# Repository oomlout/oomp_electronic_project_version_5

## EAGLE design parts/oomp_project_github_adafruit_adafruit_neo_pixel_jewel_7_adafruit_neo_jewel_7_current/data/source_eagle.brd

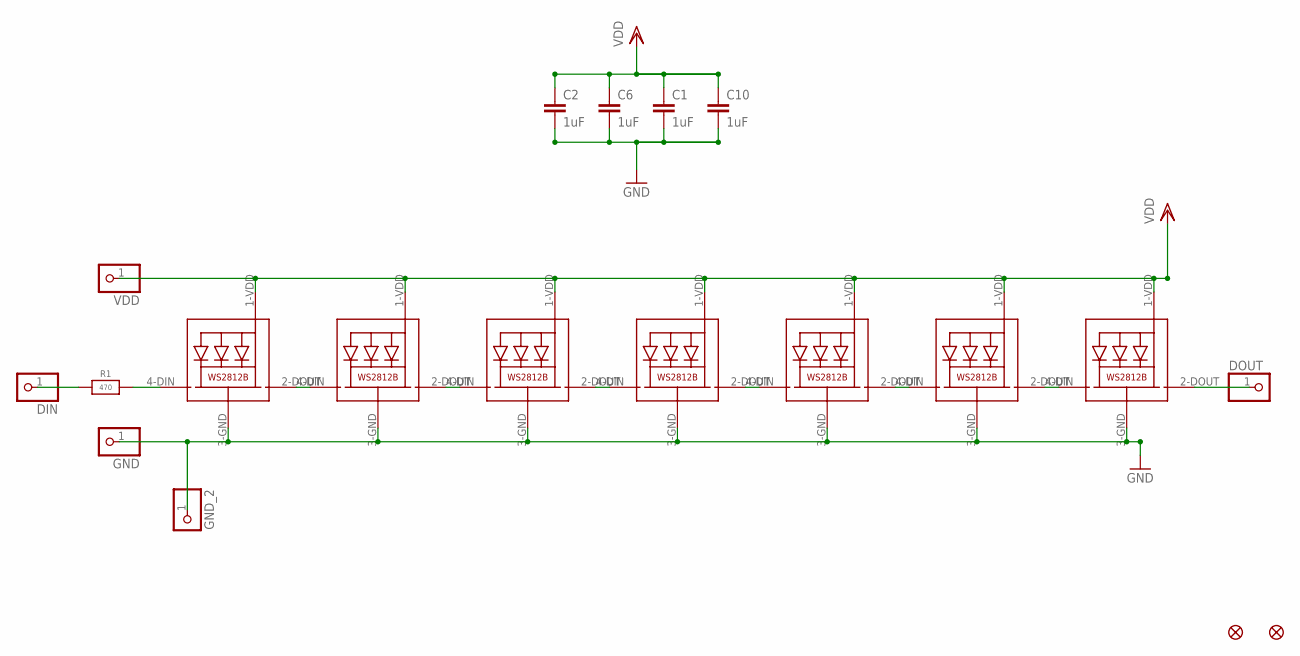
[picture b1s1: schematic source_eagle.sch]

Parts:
C1, C2, C6, C10: 1uF; C0603
DIN: PINHD-1X1CB; 1X01-CLEANBIG
DOUT: PINHD-1X1CB; 1X01-CLEANBIG
FID1, FID2: FIDUCIAL""; FIDUCIAL_1MM
GND: PINHD-1X1CB; 1X01-CLEANBIG
GND_2: PINHD-1X1CB; 1X01-CLEANBIG
LED1, LED2, LED3, LED4, LED5, LED6, LED7: WS2812B5050; WS2812B
R1: 470; 0603-NO
VDD: PINHD-1X1CB; 1X01-CLEANBIG

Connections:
GND: C1.2, C2.2, C6.2, C10.2, GND.1, GND_2.1, LED1.3-GND (GND), LED2.3-GND (GND), LED3.3-GND (GND), LED4.3-GND (GND), LED5.3-GND (GND), LED6.3-GND (GND), LED7.3-GND (GND)
unnamed: LED1.2-DOUT (DO), LED2.4-DIN (DI)
unnamed: LED2.2-DOUT (DO), LED3.4-DIN (DI)
unnamed: LED3.2-DOUT (DO), LED4.4-DIN (DI)
unnamed: LED4.2-DOUT (DO), LED5.4-DIN (DI)
unnamed: LED5.2-DOUT (DO), LED6.4-DIN (DI)
unnamed: LED6.2-DOUT (DO), LED7.4-DIN (DI)
unnamed: DOUT.1, LED7.2-DOUT (DO)
unnamed: LED1.4-DIN (DI), R1.2
unnamed: DIN.1, R1.1
VDD: C1.1, C2.1, C6.1, C10.1, LED1.1-VDD (VDD), LED2.1-VDD (VDD), LED3.1-VDD (VDD), LED4.1-VDD (VDD), LED5.1-VDD (VDD), LED6.1-VDD (VDD), LED7.1-VDD (VDD), VDD.1

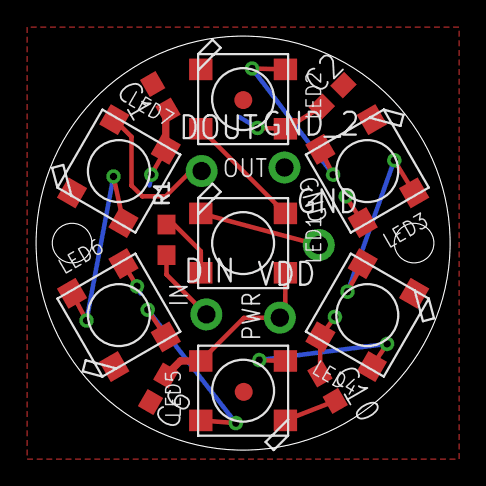
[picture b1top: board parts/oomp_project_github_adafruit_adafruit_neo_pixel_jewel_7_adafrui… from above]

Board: 2 copper layers, 23.0 x 23.0 mm, 20 parts (1 on the bottom side), 11 nets.

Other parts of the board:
U$3: ADAFRUIT_5MM

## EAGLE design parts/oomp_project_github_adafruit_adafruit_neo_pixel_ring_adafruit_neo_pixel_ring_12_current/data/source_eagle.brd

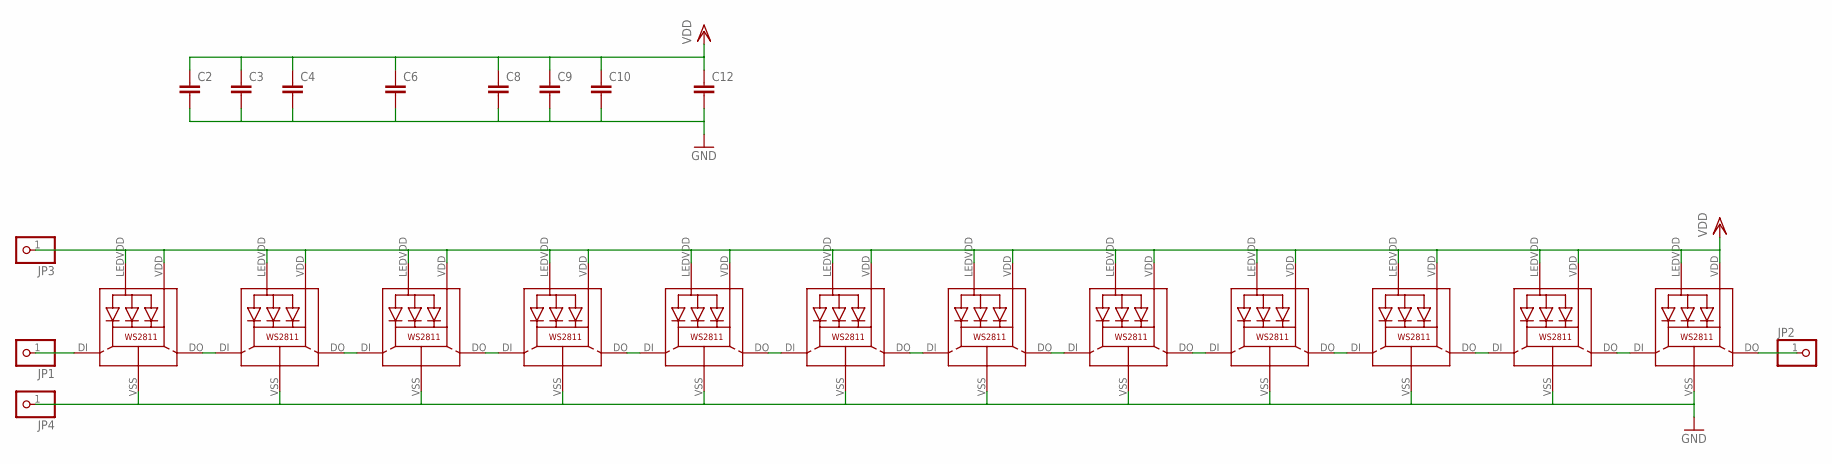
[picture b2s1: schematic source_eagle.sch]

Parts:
C2, C3, C4, C6, C8, C9, C10, C12: C-EUC0603; C0603
JP1, JP2, JP3, JP4: PINHD-1X1CB; 1X01-CLEANBIG
LED1, LED2, LED3, LED4, LED5, LED6, LED7, LED8, LED9, LED10, LED11, LED12: WS28115050

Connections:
GND: C2.2, C3.2, C4.2, C6.2, C8.2, C9.2, C10.2, C12.2, JP4.1, LED1.VSS (GND), LED2.VSS (GND), LED3.VSS (GND), LED4.VSS (GND), LED5.VSS (GND), LED6.VSS (GND), LED7.VSS (GND), LED8.VSS (GND), LED9.VSS (GND), LED10.VSS (GND), LED11.VSS (GND), LED12.VSS (GND)
unnamed: LED1.DO, LED2.DI
unnamed: LED2.DO, LED3.DI
unnamed: LED3.DO, LED4.DI
unnamed: LED4.DO, LED5.DI
unnamed: LED5.DO, LED6.DI
unnamed: LED6.DO, LED7.DI
unnamed: LED7.DO, LED8.DI
unnamed: LED8.DO, LED9.DI
unnamed: LED9.DO, LED10.DI
unnamed: LED10.DO, LED11.DI
unnamed: LED11.DO, LED12.DI
unnamed: JP1.1, LED1.DI
unnamed: JP2.1, LED12.DO
VDD: C2.1, C3.1, C4.1, C6.1, C8.1, C9.1, C10.1, C12.1, JP3.1, LED1.LEDVDD, LED1.VDD, LED2.LEDVDD, LED2.VDD, LED3.LEDVDD, LED3.VDD, LED4.LEDVDD, LED4.VDD, LED5.LEDVDD, LED5.VDD, LED6.LEDVDD, LED6.VDD, LED7.LEDVDD, LED7.VDD, LED8.LEDVDD, LED8.VDD, LED9.LEDVDD, LED9.VDD, LED10.LEDVDD, LED10.VDD, LED11.LEDVDD, LED11.VDD, LED12.LEDVDD, LED12.VDD

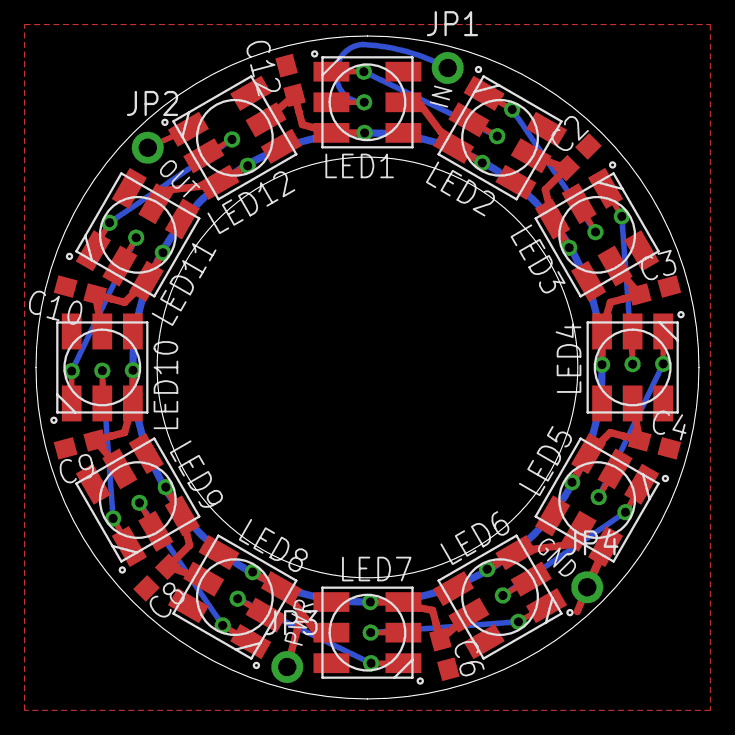
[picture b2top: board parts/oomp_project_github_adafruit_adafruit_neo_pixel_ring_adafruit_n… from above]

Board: 2 copper layers, 36.8 x 36.8 mm, 27 parts (1 on the bottom side), 15 nets.

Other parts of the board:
U$1, U$2: GUIDE-STAR-12
U$3: ADAFRUIT_5MM

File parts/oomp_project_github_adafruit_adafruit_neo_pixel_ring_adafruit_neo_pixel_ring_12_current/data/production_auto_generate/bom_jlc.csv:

Comment,Designator,Footprint,LCSC Part #
,"JP1,JP2,JP3,JP4",Adafruit NeoPixel Ring 12-import-fps:1X01-CLEANBIG,C7501259
,U$3,Adafruit NeoPixel Ring 12-import-fps:ADAFRUIT_5MM,
,"C2,C3,C4,C6,C8,C9,C10,C12",Adafruit NeoPixel Ring 12-import-fps:C0603,
,"U$1,U$2",Adafruit NeoPixel Ring 12-import-fps:GUIDE-STAR-12,
WS28115050,"LED1,LED2,LED3,LED4,LED5,LED6,LED7,LED8,LED9,LED10,LED11,LED12",Adafruit NeoPixel Ring 12-import-fps:WS28115050,

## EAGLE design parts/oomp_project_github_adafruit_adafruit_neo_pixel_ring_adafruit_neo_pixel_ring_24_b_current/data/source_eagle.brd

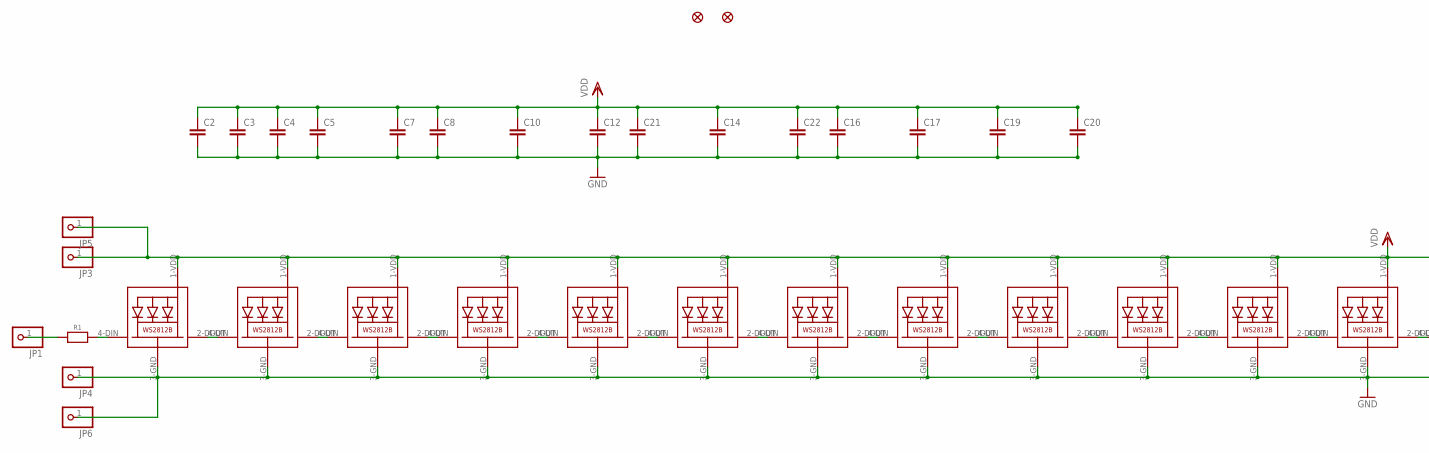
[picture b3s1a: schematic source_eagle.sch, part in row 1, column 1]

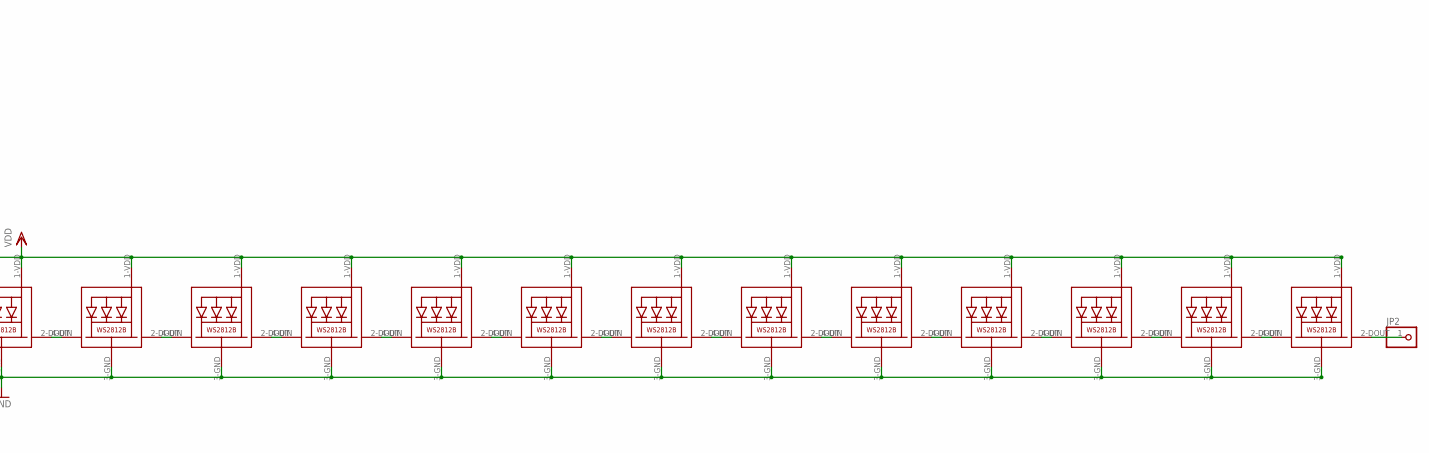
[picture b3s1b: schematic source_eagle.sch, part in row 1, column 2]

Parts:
C2, C3, C4, C5, C7, C8, C10, C12, C14, C16, C17, C19, C20, C21, C22: C-EUC0603; C0603
FID1, FID2: FIDUCIAL""; FIDUCIAL_1MM
JP1, JP2, JP3, JP4, JP5, JP6: PINHD-1X1CB; 1X01-CLEANBIG
LED1, LED2, LED3, LED4, LED5, LED6, LED7, LED8, LED9, LED10, LED11, LED12, LED13, LED14, LED15, LED16, LED17, LED18, LED19, LED20, LED21, LED22, LED23, LED24: WS2812B5050; WS2812B
R1: RESISTOR_0603_NOOUT; 0603-NO

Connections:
GND: C2.2, C3.2, C4.2, C5.2, C7.2, C8.2, C10.2, C12.2, C14.2, C16.2, C17.2, C19.2, C20.2, C21.2, C22.2, JP4.1, JP6.1, LED1.3-GND (GND), LED2.3-GND (GND), LED3.3-GND (GND), LED4.3-GND (GND), LED5.3-GND (GND), LED6.3-GND (GND), LED7.3-GND (GND), LED8.3-GND (GND), LED9.3-GND (GND), LED10.3-GND (GND), LED11.3-GND (GND), LED12.3-GND (GND), LED13.3-GND (GND), LED14.3-GND (GND), LED15.3-GND (GND), LED16.3-GND (GND), LED17.3-GND (GND), LED18.3-GND (GND), LED19.3-GND (GND), LED20.3-GND (GND), LED21.3-GND (GND), LED22.3-GND (GND), LED23.3-GND (GND), LED24.3-GND (GND)
unnamed: LED1.2-DOUT (DO), LED2.4-DIN (DI)
unnamed: LED2.2-DOUT (DO), LED3.4-DIN (DI)
unnamed: LED3.2-DOUT (DO), LED4.4-DIN (DI)
unnamed: LED4.2-DOUT (DO), LED5.4-DIN (DI)
unnamed: LED5.2-DOUT (DO), LED6.4-DIN (DI)
unnamed: LED6.2-DOUT (DO), LED7.4-DIN (DI)
unnamed: LED7.2-DOUT (DO), LED8.4-DIN (DI)
unnamed: LED8.2-DOUT (DO), LED9.4-DIN (DI)
unnamed: LED9.2-DOUT (DO), LED10.4-DIN (DI)
unnamed: LED10.2-DOUT (DO), LED11.4-DIN (DI)
unnamed: LED11.2-DOUT (DO), LED12.4-DIN (DI)
unnamed: LED12.2-DOUT (DO), LED13.4-DIN (DI)
unnamed: LED13.2-DOUT (DO), LED14.4-DIN (DI)
unnamed: LED14.2-DOUT (DO), LED15.4-DIN (DI)
unnamed: LED15.2-DOUT (DO), LED16.4-DIN (DI)
unnamed: LED16.2-DOUT (DO), LED17.4-DIN (DI)
unnamed: LED17.2-DOUT (DO), LED18.4-DIN (DI)
unnamed: LED18.2-DOUT (DO), LED19.4-DIN (DI)
unnamed: LED19.2-DOUT (DO), LED20.4-DIN (DI)
unnamed: LED20.2-DOUT (DO), LED21.4-DIN (DI)
unnamed: LED21.2-DOUT (DO), LED22.4-DIN (DI)
unnamed: LED22.2-DOUT (DO), LED23.4-DIN (DI)
unnamed: LED23.2-DOUT (DO), LED24.4-DIN (DI)
unnamed: JP2.1, LED24.2-DOUT (DO)
unnamed: LED1.4-DIN (DI), R1.2
unnamed: JP1.1, R1.1
VDD: C2.1, C3.1, C4.1, C5.1, C7.1, C8.1, C10.1, C12.1, C14.1, C16.1, C17.1, C19.1, C20.1, C21.1, C22.1, JP3.1, JP5.1, LED1.1-VDD (VDD), LED2.1-VDD (VDD), LED3.1-VDD (VDD), LED4.1-VDD (VDD), LED5.1-VDD (VDD), LED6.1-VDD (VDD), LED7.1-VDD (VDD), LED8.1-VDD (VDD), LED9.1-VDD (VDD), LED10.1-VDD (VDD), LED11.1-VDD (VDD), LED12.1-VDD (VDD), LED13.1-VDD (VDD), LED14.1-VDD (VDD), LED15.1-VDD (VDD), LED16.1-VDD (VDD), LED17.1-VDD (VDD), LED18.1-VDD (VDD), LED19.1-VDD (VDD), LED20.1-VDD (VDD), LED21.1-VDD (VDD), LED22.1-VDD (VDD), LED23.1-VDD (VDD), LED24.1-VDD (VDD)

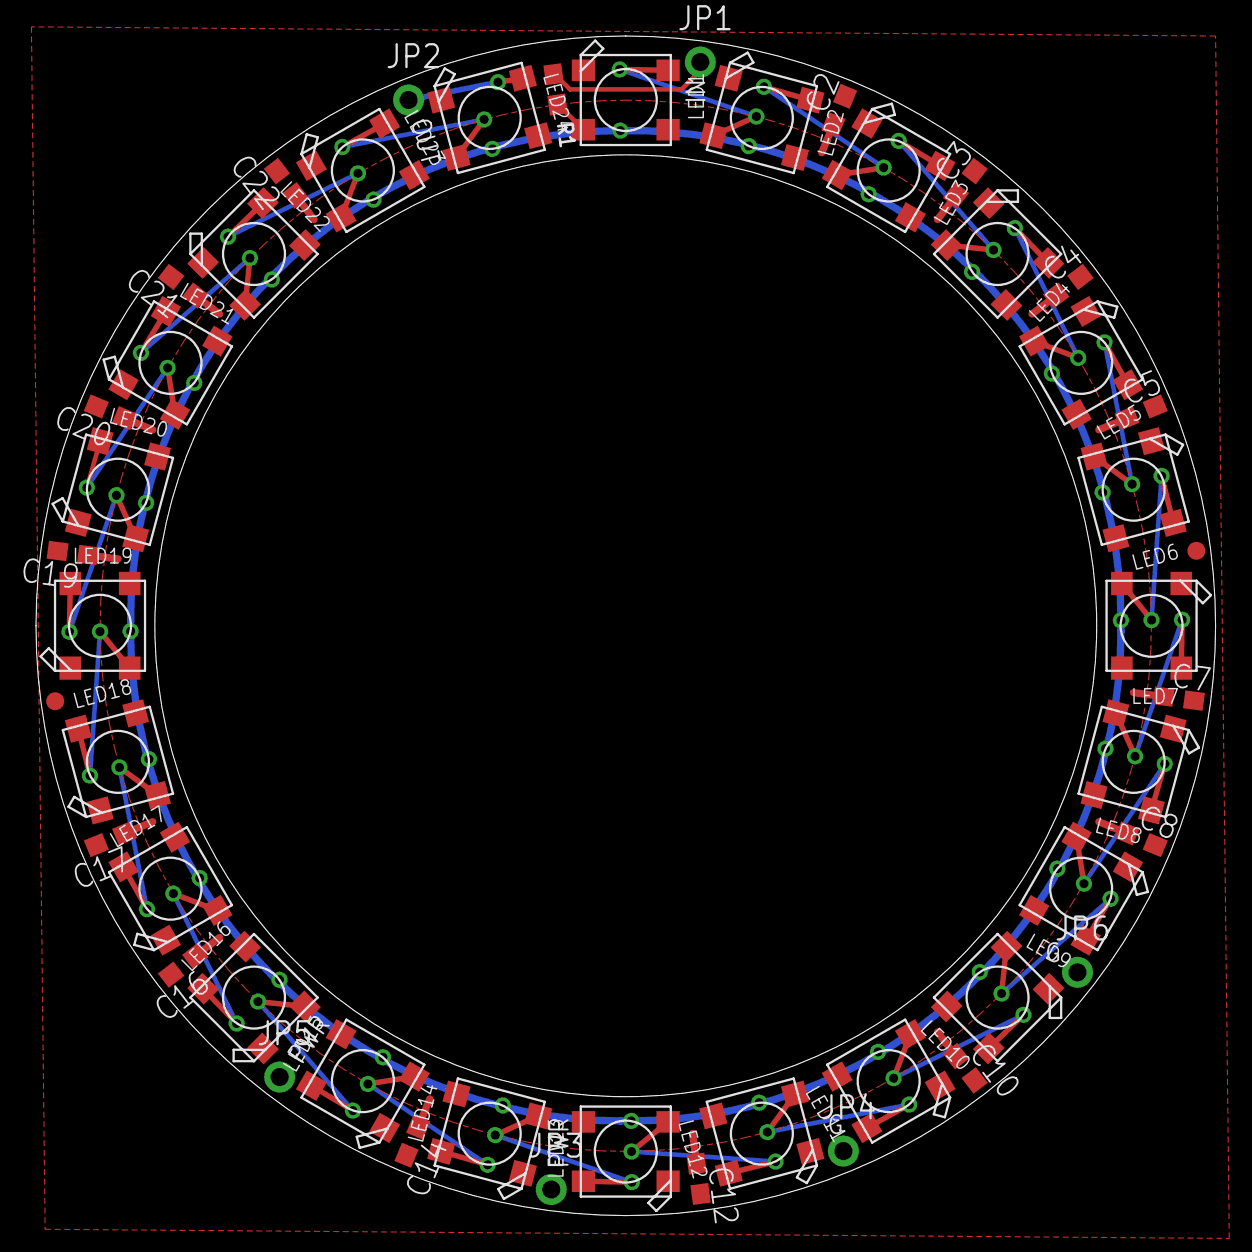
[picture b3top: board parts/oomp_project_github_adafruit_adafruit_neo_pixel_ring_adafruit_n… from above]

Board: 2 copper layers, 65.5 x 65.5 mm, 49 parts (1 on the bottom side), 28 nets.

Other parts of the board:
U$1: ADAFRUIT_5MM

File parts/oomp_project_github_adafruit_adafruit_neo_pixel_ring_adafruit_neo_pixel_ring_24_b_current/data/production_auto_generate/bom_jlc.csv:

Comment,Designator,Footprint,LCSC Part #
,R1,Adafruit NeoPixel Ring 24 B-import-fps:0603-NO,
,"JP1,JP2,JP3,JP4,JP5,JP6",Adafruit NeoPixel Ring 24 B-import-fps:1X01-CLEANBIG,C7501259
,U$1,Adafruit NeoPixel Ring 24 B-import-fps:ADAFRUIT_5MM,
,"C2,C3,C4,C5,C7,C8,C10,C12,C14,C16,C17,C19,C20,C21,C22",Adafruit NeoPixel Ring 24 B-import-fps:C0603,
WS2812B5050,"LED1,LED2,LED3,LED4,LED5,LED6,LED7,LED8,LED9,LED10,LED11,LED12,LED13,LED14,LED15,LED16,LED17,LED18,LED19,LED20,LED21,LED22,LED23,LED24",Adafruit NeoPixel Ring 24 B-import-fps:WS2812B-NARROW,

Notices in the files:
parts and their libraries:
microbuilder: This work is placed in the public domain, and may be freely used for commercial and non-commercial work with the following conditions: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
